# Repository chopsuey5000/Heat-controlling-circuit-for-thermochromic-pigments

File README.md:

# Heat-controlling-circuit-for-thermochromic-pigments

## Overview
Thermochromic inks are pigments that change color to colorless at certain temperature. There are many different types of thermochromic pigments including textile inks for textile screen printing.

You may use any heat source or your body heat to change the color of thermochromic prints. But also, we can use electricity to heat up certain parts of the fabric to achieve dynamic pattern on fabric.
When large current goes through low resistance conductive material, it emits heat. We can use this method to heat up conductive threads to change colors of the prints.

## Calculations
All conductive threads have different properties, the resistance per meter is different in all of them.
The ideal conductive threads to build a heating source are made of steel or copper.

Some __recommended conductive threads__ like Bekinox stainless steel thread from Bekaert or Copper thread from KarlGrimm.

The __best scenario would be to have a 6-50 Ohm conductive thread with a current of 300-1000 mA__ flowing through it. The time the thermochromic ink takes to change its color is directly proportional to the amount of current. For 300mA it will need more time than for 1000mA.

To __calculate the voltage__ we just need to use ohm's law formula:

Voltage equals Current times Resistance or V = I x R

We know our conductive thread resistance(measured with the multimeter), for example 32 ohm, the current has to be a value from 300mA to 1000mA.

__For 300mA:__

__V = 0,3 * 32 => V = 9,6V__

__For 1000mA:__

__V = 1 * 32 => V = 32V__

## One conductive thread test circuit

### Materials
- Arduino UNO board
- Transistor, TIP122 or IRLZ24N or IRLB8743
- Conductive thread
- Jumper wires
- Protoboard
- Variable DC power supply

### Wiring

### Code - [view](code/_1_thread_test/)

```c++
int btnPin = 7;
int mosfetPin = 9;

void setup() {
  // put your setup code here, to run once:
  pinMode(btnPin,INPUT_PULLUP);
  pinMode(mosfetPin,OUTPUT);
  Serial.begin(9600);
}

void loop() {
  // put your main code here, to run repeatedly:
  int btnState = digitalRead(btnPin); //reads a stores button state
  if(btnState==LOW){
    //button is pressed, so START heating up the conductive thread
    digitalWrite(mosfetPin,HIGH);
  }else{
    //button is released, so STOP heating up the conductive thread
    digitalWrite(mosfetPin,LOW);
  }
}
```

## Multiple conductive threads circuit

### Materials
- Arduino MKR1000
- 8x Transistor BC817
- 8x Conductive thread

### PCB

[schematic & board design files](pcb/)

### Code - [view](code/_8_threads_test/)

```c++
#define numStrings 8

int actualString = 0;
int actualTime;
int intervalON = 8000;
int intervalOFF = 10000;
boolean state = 0;

const int pins[numStrings] = {
  9,8,7,6,5,4,3,2
};

const int timeON[numStrings] = {
  7000,9000,10000,10000,5000,6500,8000,10000
};

void setup() {
  // put your setup code here, to run once: 
  Serial.begin(9600);

  for(int i=0;i<numStrings;i++){
    pinMode(pins[i],OUTPUT);
  }

  actualTime = millis();
  
}

void loop() {
  // put your main code here, to run repeatedly:
  if(state==0 && millis()<(actualTime+timeON[actualString]))
  {
    int left = (actualTime+timeON[actualString])-millis();
    Serial.print("ON ");
    Serial.print(" : ");
    Serial.print(actualString);
    Serial.print(" : ");
    Serial.println(left);
    analogWrite(pins[actualString],255);
  }else if (state==0 && millis()>(actualTime+intervalON)){
    actualTime = millis();
    state=1;
  }

  if(state==1 && millis()<(actualTime+intervalOFF))
  {
    int left = (actualTime+intervalOFF)-millis();
    Serial.print("OFF ");
    Serial.print(" : ");
    Serial.print(actualString);
    Serial.print(" : ");
    Serial.println(left);
    analogWrite(pins[actualString],0);
  }else if (state==1 && millis()>(actualTime+intervalOFF)){
    actualTime = millis();
    state=0;
    actualString++;
    if(actualString>=8){
      actualString=0;
      Serial.println("stop");
      delay(10000);
    }
  }
}
```

```## Powering

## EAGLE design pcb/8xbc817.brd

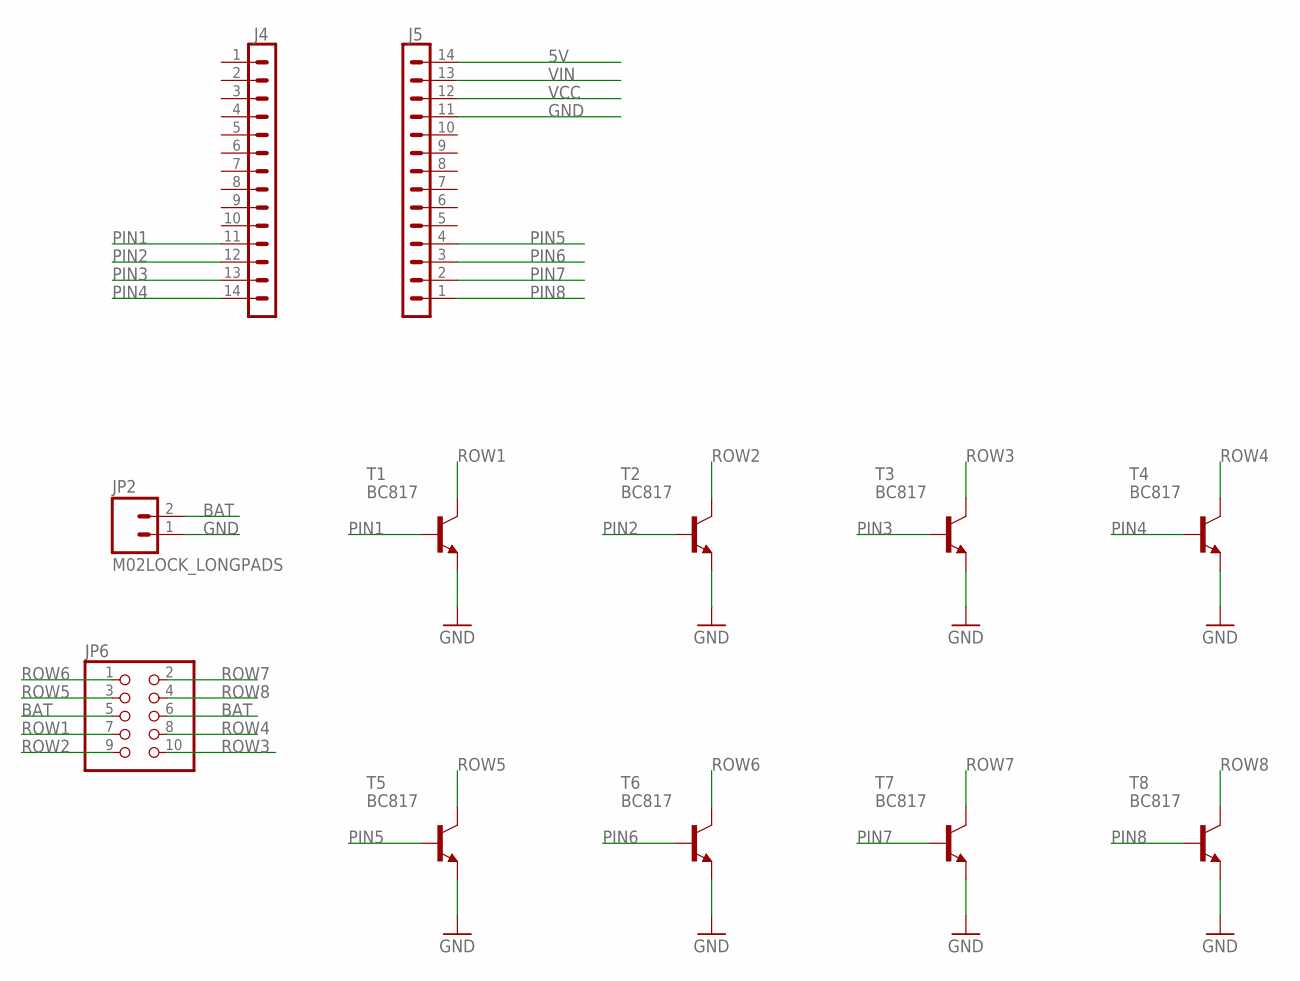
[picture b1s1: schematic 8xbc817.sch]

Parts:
J4, J5: DNP; STRIP-14-MODULI-A11
JP2: M02LOCK_LONGPADS; 1X02_LOCK_LONGPADS
JP6: PINHD-2X5; 2X05
T1, T2, T3, T4, T5, T6, T7, T8: BC817; SOT23

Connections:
5V: J5.14
BAT: JP2.2, JP6.5, JP6.6
GND: J5.11, JP2.1, T1.2 (E), T2.2 (E), T3.2 (E), T4.2 (E), T5.2 (E), T6.2 (E), T7.2 (E), T8.2 (E)
PIN1: J4.11, T1.1 (B)
PIN2: J4.12, T2.1 (B)
PIN3: J4.13, T3.1 (B)
PIN4: J4.14, T4.1 (B)
PIN5: J5.4, T5.1 (B)
PIN6: J5.3, T6.1 (B)
PIN7: J5.2, T7.1 (B)
PIN8: J5.1, T8.1 (B)
ROW1: JP6.7, T1.3 (C)
ROW2: JP6.9, T2.3 (C)
ROW3: JP6.10, T3.3 (C)
ROW4: JP6.8, T4.3 (C)
ROW5: JP6.3, T5.3 (C)
ROW6: JP6.1, T6.3 (C)
ROW7: JP6.2, T7.3 (C)
ROW8: JP6.4, T8.3 (C)
VCC: J5.12
VIN: J5.13

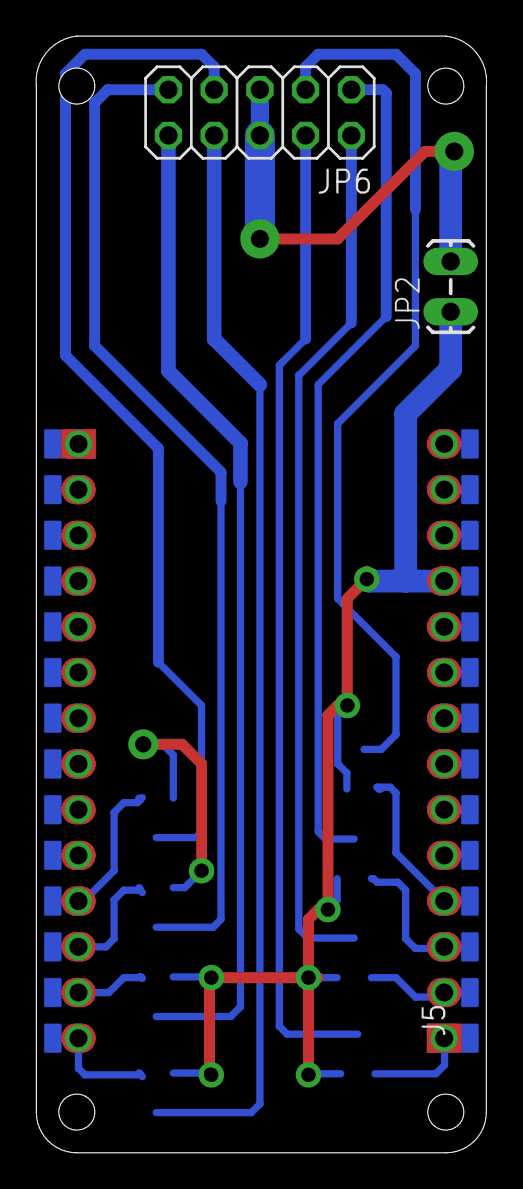
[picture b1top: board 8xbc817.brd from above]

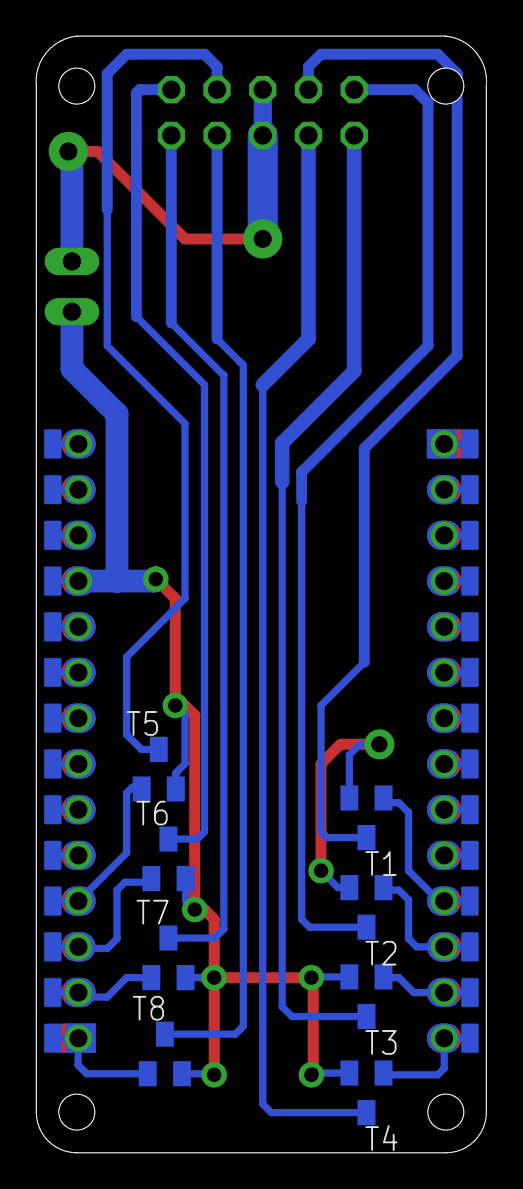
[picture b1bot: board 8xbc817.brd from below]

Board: 2 copper layers, 25.0 x 62.0 mm, 12 parts (8 on the bottom side), 18 nets.

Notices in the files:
parts and their libraries:
SparkFun-Connectors: Licensing: CC v3.0 Share-Alike You are welcome to use this library for commercial purposes.
SparkFun-Aesthetics: Licensing: Creative Commons ShareAlike 4.0 International - https://creativecommons.org/licenses/by-sa/4.0
